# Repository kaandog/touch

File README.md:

repo for touch

549website: directory for the 549 project web page.
server: directory for the server that will handle communication between nodes and the app.
iOSApp: directory for all the iOS app related code
firmware: directory for the node firmware

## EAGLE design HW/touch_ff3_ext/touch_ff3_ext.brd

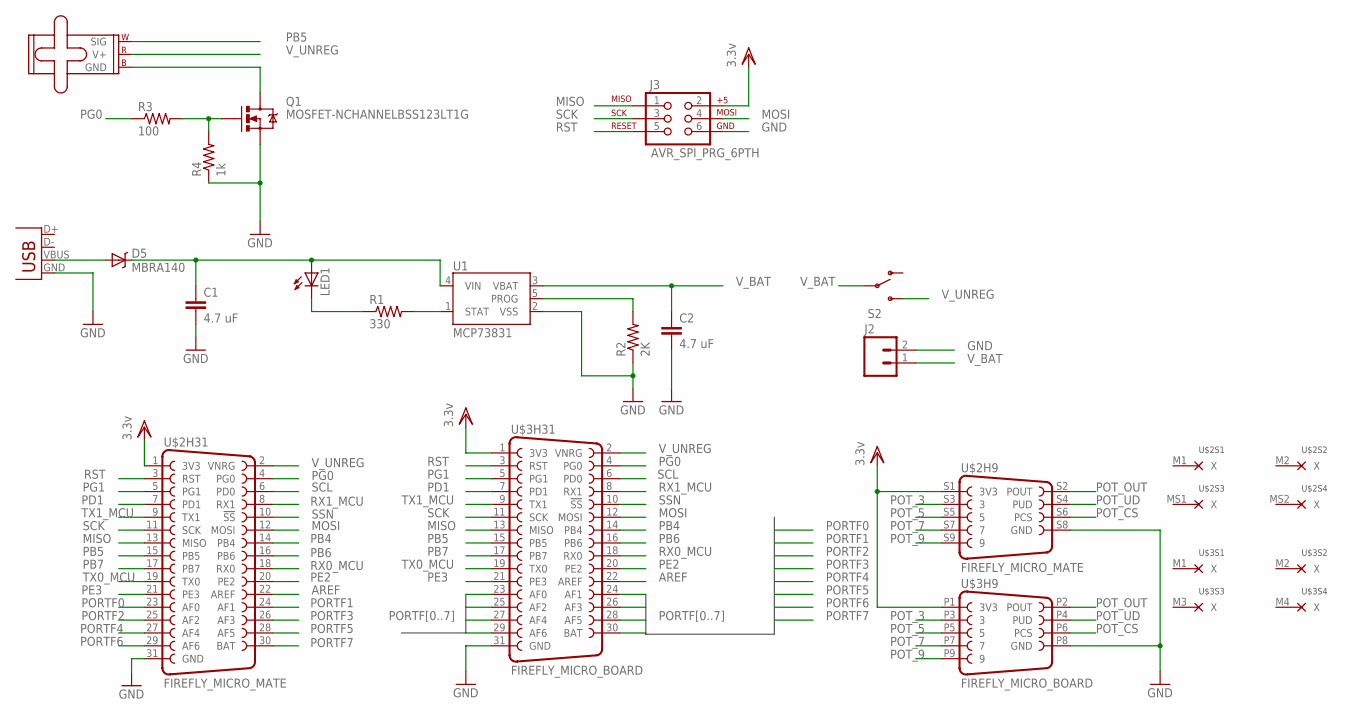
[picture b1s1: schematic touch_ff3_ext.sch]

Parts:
C1, C2: 4.7 uF; 1206
D5: MBRA140; SMA-DIODE
J2: M02PTH; 1X02
J3: AVR_SPI_PRG_6PTH; 2X3
LED1: LED1206; LED-1206
M1: SMALL_SERVO; 1X03
Q1: MOSFET-NCHANNELBSS123LT1G; SOT23-3
R1: 330; 1206
R2: 2K; 1206
R3: 100; 1206
R4: 1k; 1206
S2: SWITCH-SPDT-SMD-A; SWITCH-SPST-SMD-A
U1: MCP73831; SOT23-5
U$2: FIREFLY_MICRO_MATE
U$3: FIREFLY_MICRO_BOARD
X1: USBSMD; USB-MINIB

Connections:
AREF: U$2.22 (AREF), U$3.22 (AREF)
GND: C1.2, C2.2, J2.2, J3.6, Q1.2 (S), R2.1, R4.1, U1.2 (VSS), U$2.31 (GND), U$2.S8 (GND), U$3.31 (GND), U$3.P8 (GND), X1.GND
MISO: J3.1, U$2.13 (MISO), U$3.13 (MISO)
MOSI: J3.4, U$2.12 (MOSI), U$3.12 (MOSI)
unnamed: M1.3 (GND), Q1.3 (D)
unnamed: Q1.1 (G), R3.2, R4.2
unnamed: C1.1, D5.C, LED1.A, U1.4 (VIN)
unnamed: R1.2, U1.1 (STAT)
unnamed: LED1.C, R1.1
unnamed: D5.A, X1.VBUS
unnamed: R2.2, U1.5 (PROG)
PB4: U$2.14 (PB4), U$3.14 (PB4)
PB5: M1.1 (SIG), U$2.15 (PB5), U$3.15 (PB5)
PB6: U$2.16 (PB6), U$3.16 (PB6)
PB7: U$2.17 (PB7), U$3.17 (PB7)
PD1: U$2.7 (PD1), U$3.7 (PD1)
PE2: U$2.20 (PE2), U$3.20 (PE2)
PE3: U$2.21 (PE3), U$3.21 (PE3)
PG0: R3.1, U$2.4 (PG0), U$3.4 (PG0)
PG1: U$2.5 (PG1), U$3.5 (PG1)
PORTF0: U$2.23 (AF0), U$3.23 (AF0)
PORTF1: U$2.24 (AF1), U$3.24 (AF1)
PORTF2: U$2.25 (AF2), U$3.25 (AF2)
PORTF3: U$2.26 (AF3), U$3.26 (AF3)
PORTF4: U$2.27 (AF4), U$3.27 (AF4)
PORTF5: U$2.28 (AF5), U$3.28 (AF5)
PORTF6: U$2.29 (AF6), U$3.29 (AF6)
PORTF7: U$2.30 (BAT), U$3.30 (BAT)
POT_3: U$2.S3 (3), U$3.P3 (3)
POT_5: U$2.S5 (5), U$3.P5 (5)
POT_7: U$2.S7 (7), U$3.P7 (7)
POT_9: U$2.S9 (9), U$3.P9 (9)
POT_CS: U$2.S6 (PCS), U$3.P6 (PCS)
POT_OUT: U$2.S2 (POUT), U$3.P2 (POUT)
POT_UD: U$2.S4 (PUD), U$3.P4 (PUD)
RST: J3.5, U$2.3 (RST), U$3.3 (RST)
RX0_MCU: U$2.18 (RX0), U$3.18 (RX0)
RX1_MCU: U$2.8 (RX1), U$3.8 (RX1)
SCK: J3.3, U$2.11 (SCK), U$3.11 (SCK)
SCL: U$2.6 (PD0), U$3.6 (PD0)
SSN: U$2.10 (!SS), U$3.10 (!SS)
TX0_MCU: U$2.19 (TX0), U$3.19 (TX0)
TX1_MCU: U$2.9 (TX1), U$3.9 (TX1)
VDD: J3.2, U$2.1 (3V3), U$2.S1 (3V3), U$3.1 (3V3), U$3.P1 (3V3)
V_BAT: C2.1, J2.1, S2.2, U1.3 (VBAT)
V_UNREG: M1.2 (V+), S2.3 (S), U$2.2 (VNRG), U$3.2 (VNRG)

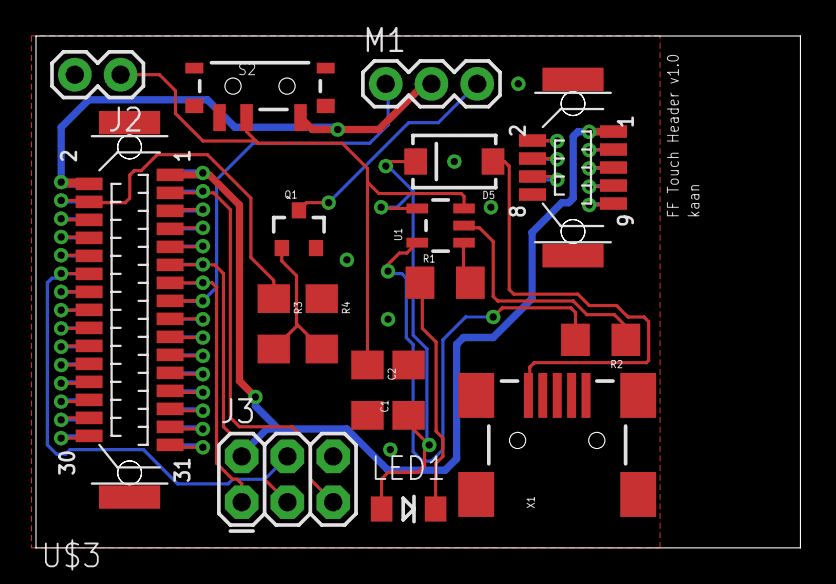
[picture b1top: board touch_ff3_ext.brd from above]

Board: 2 copper layers, 42.5 x 28.4 mm, 17 parts (1 on the bottom side), 46 nets.

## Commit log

2016-02-18 basic repo structure
2016-02-18 readme fix
2016-02-18 initial website
2016-02-19 improvements
2016-02-19 add designs
2016-02-19 stuff
2016-02-19 gucci
2016-02-19 another touch
2016-02-20 add requirements/goals
2016-02-20 tech specs
2016-02-29 added initial extension board schematic
2016-03-02 Add boilerplate for cloud code
2016-03-16 Webserver code
2016-03-16 iOS ready go
2016-03-16 rasp server code
2016-03-17 added header boards
2016-03-17 updated gitignore
2016-03-18 .DS_Store removed, added first servo demo code
2016-03-19 serial read/write and firmware for first demo
2016-03-19 Integrated with serial write
2016-03-20 Mobile app
2016-03-20 remove sub project
2016-03-20 Add iOS code
2016-03-20 some touches
2016-03-21 Add persistant storage
2016-03-21 updated pcb, removed .swp file from fw dir
2016-03-21 updated transistor, routed 1 last connection, added vias to balance out gnd planes
2016-03-21 change vdd/vunreg wire widths
2016-03-23 Got collectionview to work
2016-03-23 got up/down button to work for each node
2016-03-25 demo 2 rf stuff started
2016-03-28 more demo 2 stuff
2016-03-28 First iteration of solidwork design
2016-03-28 First iteration of solidworks design
2016-03-29 basic rf working, need to figure out aes, crc, pan, channel mac address fml
2016-03-29 updated git ignore, added state transition functions
2016-04-03 2nd Iteration of case. Was 3d Printed. 1st Iteration of head connector.
2016-04-04 added new case done with rhino
2016-04-04 rf servo control now working
2016-04-04 minor servo calib
2016-04-06 cleaned up and printed micro case
2016-04-09 Add dots + arm to the gear
2016-04-09 Degree up/down functionality + design assets for iOS
2016-04-10 added raspi case
2016-04-10 added node for new servos
2016-04-14 updated pcb, added servo on off code
2016-04-18 Resized RasPi case and Node case for new servo/battery
2016-04-18 Added stl files of router case
2016-04-18 Uploaded correct raspi/router STL file
2016-04-18 STL Router Cover file
2016-04-18 Router Top STL File
2016-04-18 RasPi Bot STL File
2016-04-20 picode for multiple users
2016-04-23 servo on/off, works with micro firefly, need to add mac addresses and duty cyclinc
2016-04-24 started adding commands and node_ids
2016-04-25 more design assets
2016-04-25 updated rhino model
2016-04-25 more assets
2016-04-25 added logo to node case
2016-04-26 moved to new packet structure
2016-04-26 new node case with arm and number
2016-04-26 added new stls, added modular arm stuff
2016-04-27 new arm model, new parts that have to be printed are in STL/ read the readme
2016-04-27 Login view + fetch nodes from cloud + setup the table for alarms
2016-04-27 added abstraction layer for touch // added ack and retry
2016-04-27 Updated url + animations
2016-04-27 new cloud code + more assets
2016-04-28 animations
2016-04-28 sleep and wakeup now works
2016-04-28 Switch arm header, see if measurements are correct.
2016-04-28 Add alarm functionality + fixes
2016-04-28 UPDATED: Switch arm now stays in place better
2016-04-29 mid debug commit
2016-04-29 added some new stuff
2016-04-29 Readjust sizes
2016-04-29 1st Iteration of new arm
2016-04-29 moved wakeup handling to gateway
2016-04-29 added tristating
2016-04-29 Testing new slot header
2016-04-29 2nd iteration of slotted header with a better fit
2016-04-29 Make it based on position
2016-04-29 1st Iteration
2016-04-29 server stable
2016-04-29 first relatively stable commit
2016-04-29 more stable, fixed bug for 3rd node
2016-04-30 Added files via upload
2016-04-30 Final Iteration
2016-04-30 Thicker overhead
2016-04-30 Arm for sliding switches
2016-04-30 1st Iteration of final design
2016-04-30 stable server!
2016-04-30 lotta new features
2016-05-01 stable, will add e,0,x e,1,x now
2016-05-01 added node reachability code
2016-05-02 added hw image with and without albels
2016-05-09 Website updates
2016-05-10 updated website/added new fontawesome

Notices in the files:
parts and their libraries:
SparkFun-Aesthetics: Licensing: Creative Commons ShareAlike 4.0 International - https://creativecommons.org/licenses/by-sa/4.0
SparkFun-Resistors: Licensing: CC v3.0 Share-Alike You are welcome to use this library for commercial purposes.
